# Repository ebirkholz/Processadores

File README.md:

# Processadores
Repositório para a cadeira de Laboratório de Processadores

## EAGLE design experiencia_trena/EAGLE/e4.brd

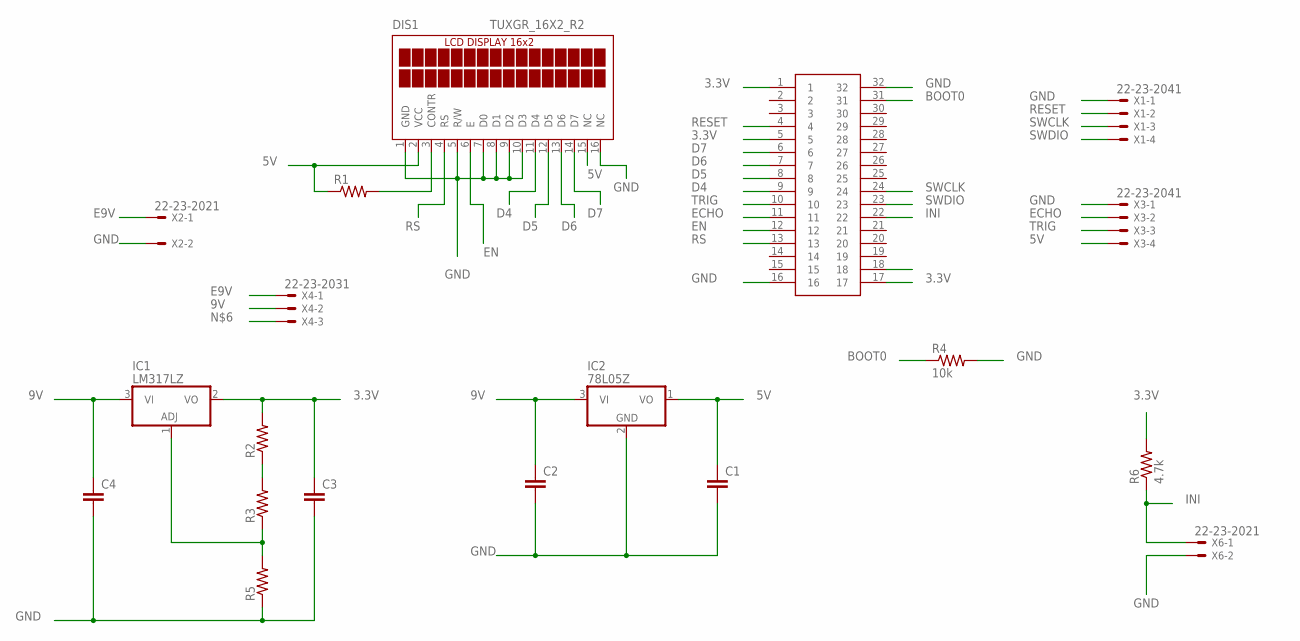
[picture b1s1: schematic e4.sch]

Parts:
C1, C2, C3, C4: C2,5-3; C2.5-3
DIS1: TUXGR_16X2_R2
IC1: LM317LZ; TO92
IC2: 78L05Z; TO92
R1, R2, R3, R5: R-US_0207/5V; 0207/5V
R4: 10k; 0207/5V
R6: 4.7k; 0207/5V
U$1: MODULO_CORTEX_M0
X1, X3: 22-23-2041
X2, X6: 22-23-2021
X4: 22-23-2031

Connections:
3.3V: C3.1, IC1.2 (VO), R2.2, R6.2, U$1.1, U$1.5, U$1.17
5V: C1.1, DIS1.2 (VCC), DIS1.15 (NC), IC2.1 (VO), R1.1, X3.4
9V: C2.1, C4.1, IC1.3 (VI), IC2.3 (VI), X4.2
BOOT0: R4.1, U$1.31
D4: DIS1.11 (D4), U$1.9
D5: DIS1.12 (D5), U$1.8
D6: DIS1.13 (D6), U$1.7
D7: DIS1.14 (D7), U$1.6
E9V: X2.1, X4.1
ECHO: U$1.11, X3.2
EN: DIS1.6 (E), U$1.12
GND: C1.2, C2.2, C3.2, C4.2, DIS1.1 (GND), DIS1.5 (R/W), DIS1.7 (D0), DIS1.8 (D1), DIS1.9 (D2), DIS1.10 (D3), DIS1.16 (NC), IC2.2 (GND), R4.2, R5.1, U$1.16, U$1.32, X1.1, X2.2, X3.1, X6.2
INI: R6.1, U$1.22, X6.1
unnamed: R2.1, R3.2
unnamed: DIS1.3 (CONTR), R1.2
unnamed: IC1.1 (ADJ), R3.1, R5.2
RESET: U$1.4, X1.2
RS: DIS1.4 (RS), U$1.13
SWCLK: U$1.24, X1.3
SWDIO: U$1.23, X1.4
TRIG: U$1.10, X3.3

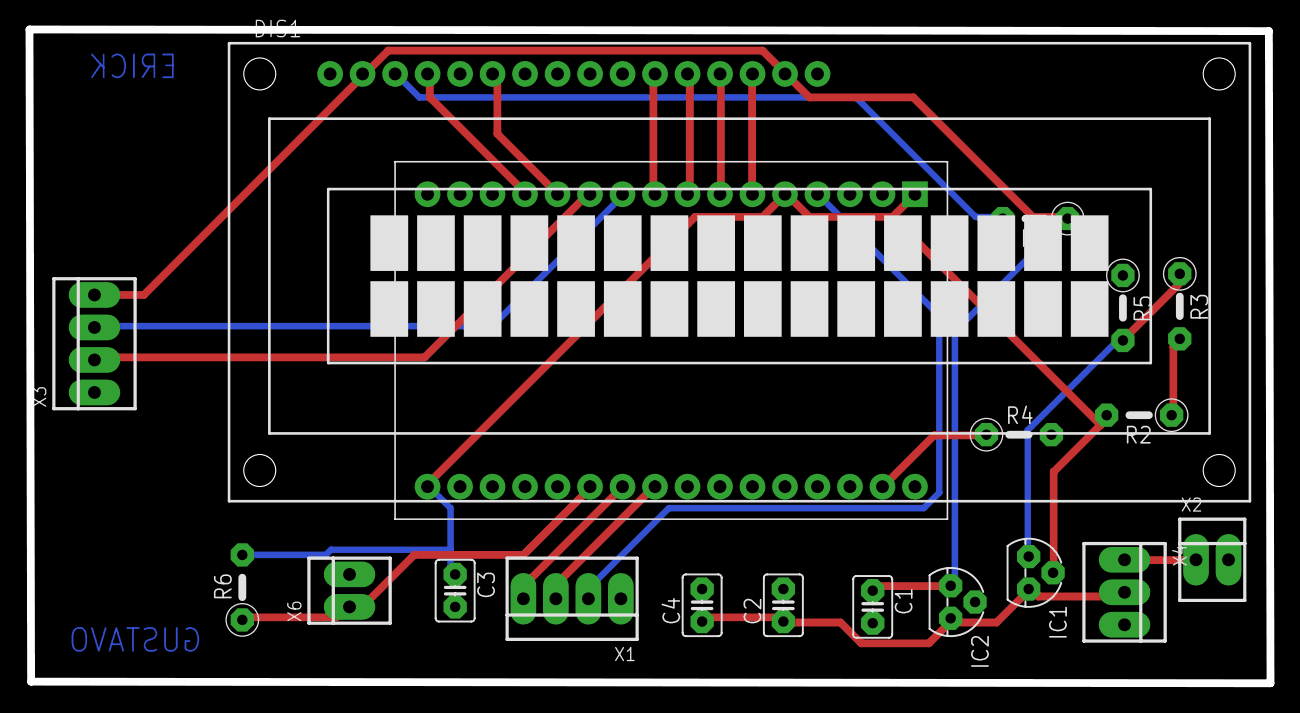
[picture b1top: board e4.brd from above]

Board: 2 copper layers, 97.0 x 51.1 mm, 19 parts (0 on the bottom side), 21 nets.

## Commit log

2017-06-14 Pasta contendo os arquivos para a Experiencia 4 - Estufa termica
2017-06-14 Pasta contendo os arquivos para a Experiencia Final - Trena Eletrica
2017-06-14 Adicionado as funcoes basicas do I2C
